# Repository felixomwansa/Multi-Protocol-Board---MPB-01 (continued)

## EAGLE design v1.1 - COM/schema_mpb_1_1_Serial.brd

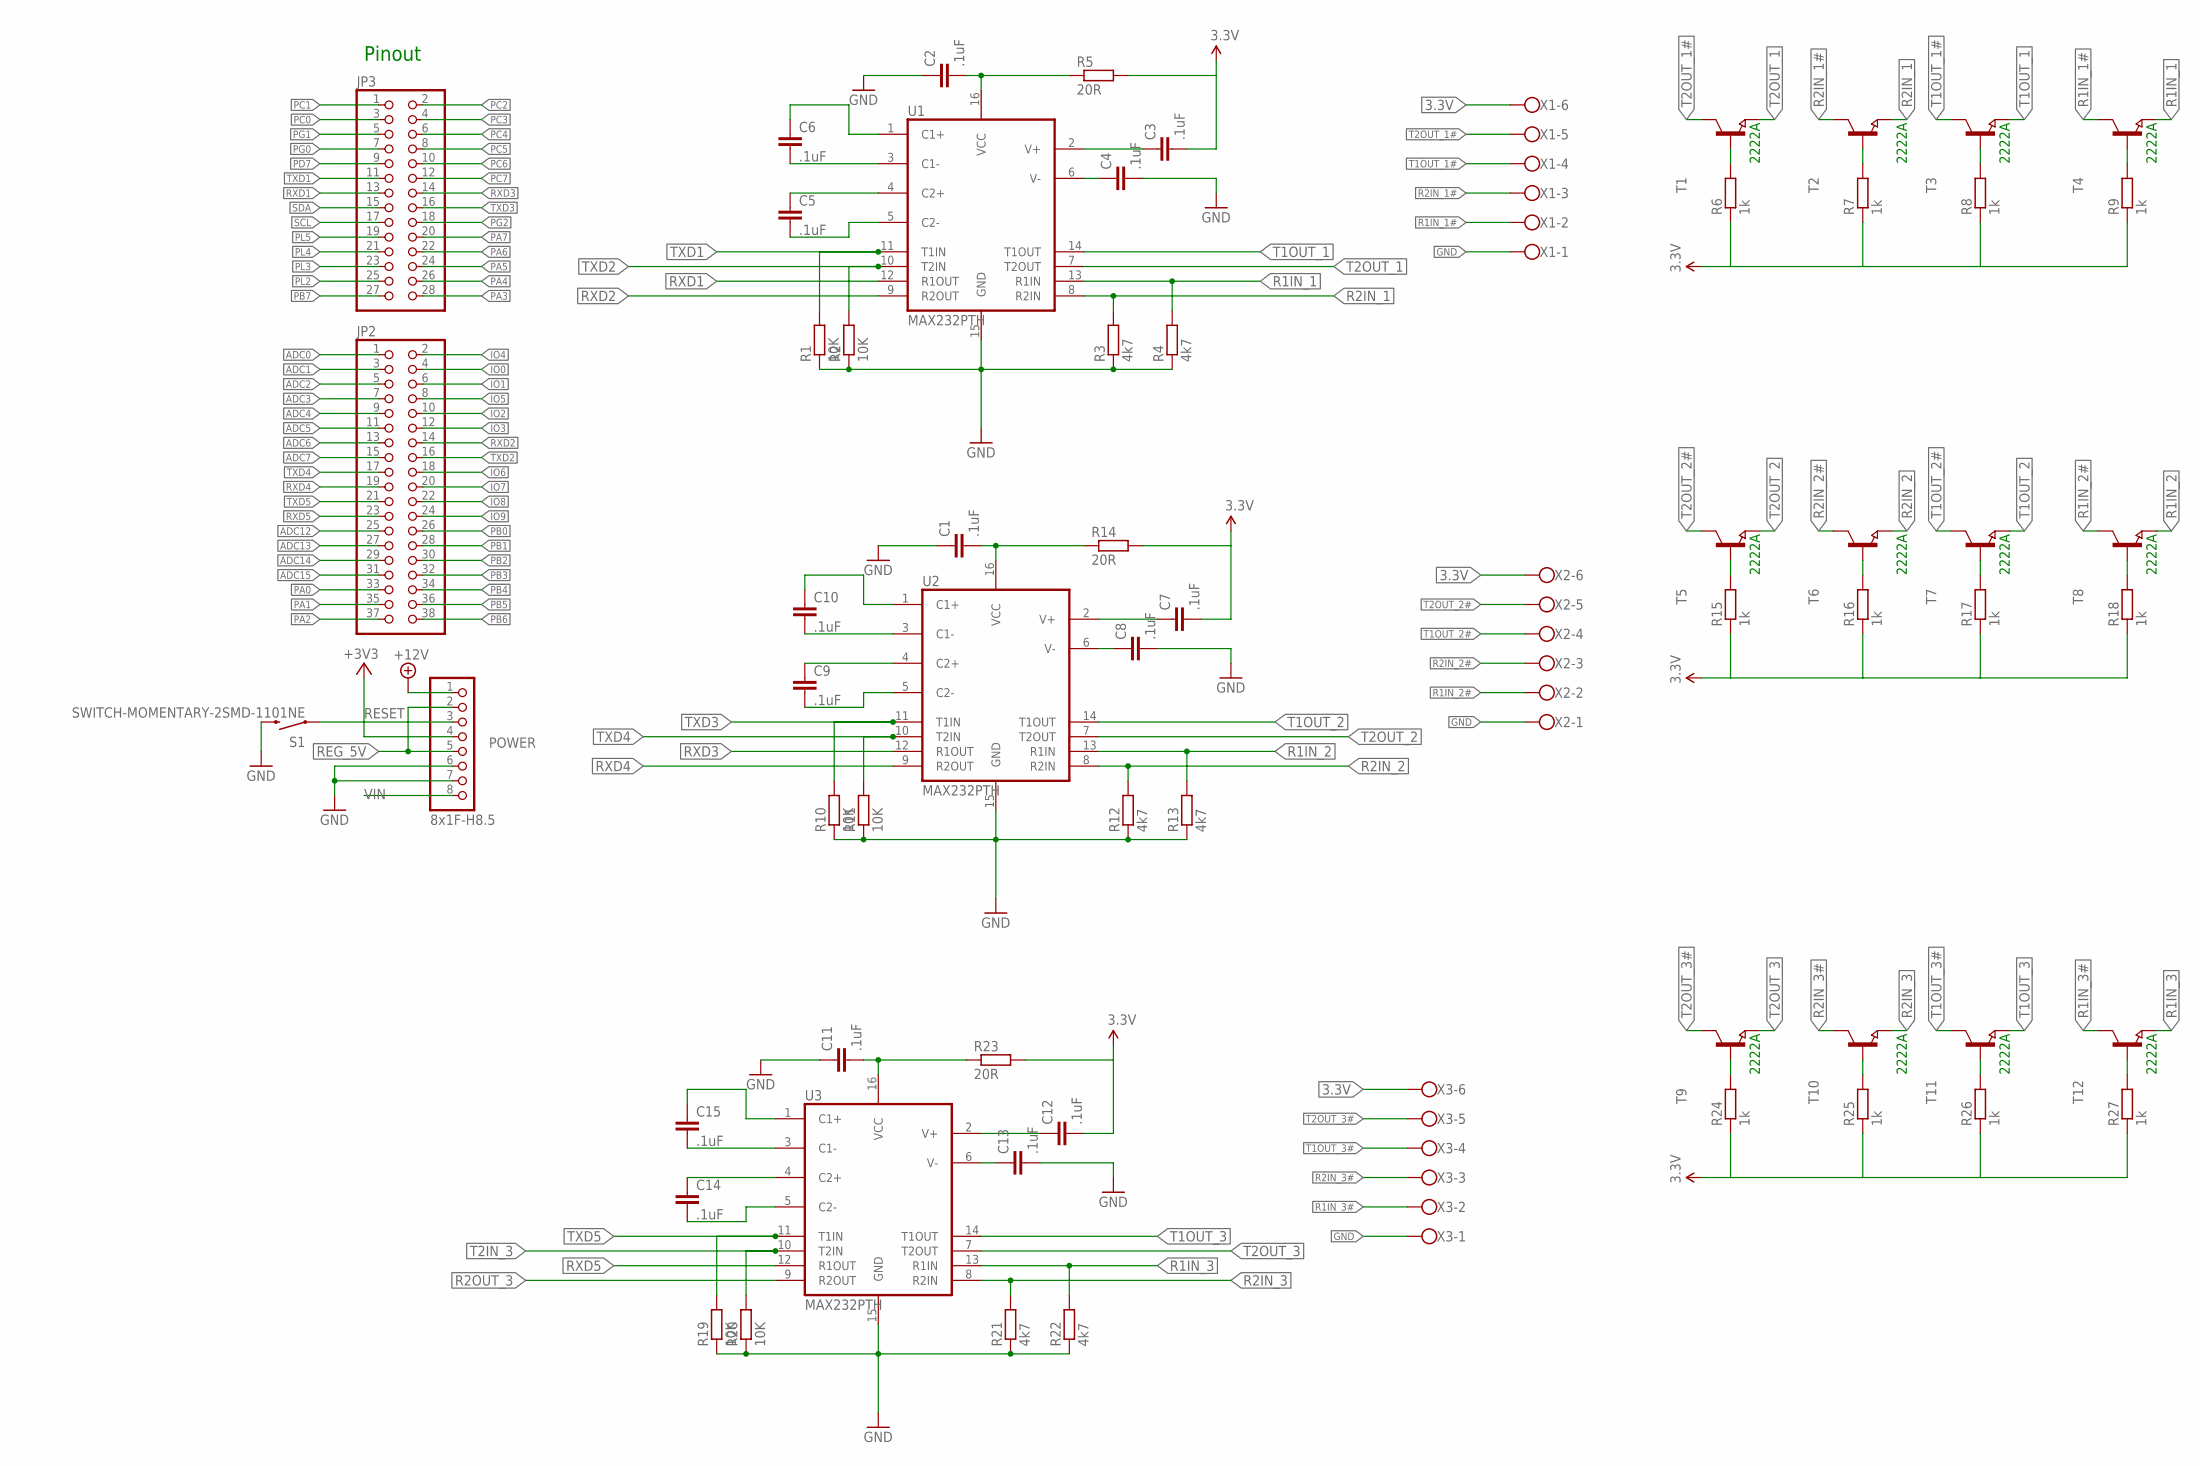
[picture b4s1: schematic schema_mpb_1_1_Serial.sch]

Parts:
C1, C2, C3, C4, C5, C6, C7, C8, C9, C10, C11, C12, C13, C14, C15: .1uF; C0805
JP2: PINHD-2X19; 2X19
JP3: PINHD-2X14; 2X14
POWER: 8x1F-H8.5; 1X08
R1, R2, R10, R11, R19, R20: 10K; R0805
R3, R4, R12, R13, R21, R22: 4k7; R0805
R5, R14, R23: 20R; R0805
R6, R7, R8, R9, R15, R16, R17, R18, R24, R25, R26, R27: 1k; R0805
S1: SWITCH-MOMENTARY-2SMD-1101NE; TACTILE-SWITCH-1101NE
T1, T2, T3, T4, T5, T6, T7, T8, T9, T10, T11, T12: NPN-TRANSISTOR_SOT23; SOT23
U1, U2, U3: MAX232PTH; DIL16
X1, X2, X3: W237-6

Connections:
3.3V: C3.2, C7.2, C12.2, POWER.4, R5.2, R6.1, R7.1, R8.1, R9.1, R14.2, R15.1, R16.1, R17.1, R18.1, R23.2, R24.1, R25.1, R26.1, R27.1, X1.6, X2.6, X3.6
+12V: POWER.1
ADC0: JP2.1
ADC1: JP2.3
ADC2: JP2.5
ADC3: JP2.7
ADC4: JP2.9
ADC5: JP2.11
ADC6: JP2.13
ADC7: JP2.15
ADC12: JP2.25
ADC13: JP2.27
ADC14: JP2.29
ADC15: JP2.31
GND: C1.1, C2.1, C4.2, C8.2, C11.1, C13.2, POWER.6, POWER.7, R1.1, R2.1, R3.1, R4.1, R10.1, R11.1, R12.1, R13.1, R19.1, R20.1, R21.1, R22.1, S1.2, U1.15 (GND), U2.15 (GND), U3.15 (GND), X1.1, X2.1, X3.1
IO0: JP2.4
IO1: JP2.6
IO2: JP2.10
IO3: JP2.12
IO4: JP2.2
IO5: JP2.8
IO6: JP2.18
IO7: JP2.20
IO8: JP2.22
IO9: JP2.24
unnamed: C10.2, U2.3 (C1-)
unnamed: C10.1, U2.1 (C1+)
unnamed: C9.2, U2.5 (C2-)
unnamed: C9.1, U2.4 (C2+)
unnamed: C8.1, U2.6 (V-)
unnamed: C1.2, R14.1, U2.16 (VCC)
unnamed: C7.1, U2.2 (V+)
unnamed: R15.2, T5.1 (B)
unnamed: R16.2, T6.1 (B)
unnamed: R17.2, T7.1 (B)
unnamed: R18.2, T8.1 (B)
unnamed: C15.2, U3.3 (C1-)
unnamed: C15.1, U3.1 (C1+)
unnamed: C14.2, U3.5 (C2-)
unnamed: C6.2, U1.3 (C1-)
unnamed: C6.1, U1.1 (C1+)
unnamed: C5.2, U1.5 (C2-)
unnamed: C5.1, U1.4 (C2+)
unnamed: C4.1, U1.6 (V-)
unnamed: C2.2, R5.1, U1.16 (VCC)
unnamed: C3.1, U1.2 (V+)
unnamed: R6.2, T1.1 (B)
unnamed: R7.2, T2.1 (B)
unnamed: R8.2, T3.1 (B)
unnamed: R9.2, T4.1 (B)
unnamed: C14.1, U3.4 (C2+)
unnamed: C13.1, U3.6 (V-)
unnamed: C11.2, R23.1, U3.16 (VCC)
unnamed: C12.1, U3.2 (V+)
unnamed: R24.2, T9.1 (B)
unnamed: R25.2, T10.1 (B)
unnamed: R26.2, T11.1 (B)
unnamed: R27.2, T12.1 (B)
PA0: JP2.33
PA1: JP2.35
PA2: JP2.37
PA3: JP3.28
PA4: JP3.26
PA5: JP3.24
PA6: JP3.22
PA7: JP3.20
PB0: JP2.26
PB1: JP2.28
PB2: JP2.30
PB3: JP2.32
PB4: JP2.34
PB5: JP2.36
PB6: JP2.38
PB7: JP3.27
PC0: JP3.3
PC1: JP3.1
PC2: JP3.2
PC3: JP3.4
PC4: JP3.6
PC5: JP3.8
PC6: JP3.10
PC7: JP3.12
PD7: JP3.9
PG0: JP3.7
PG1: JP3.5
PG2: JP3.18
PL2: JP3.25
PL3: JP3.23
PL4: JP3.21
PL5: JP3.19
R1IN_1: R4.2, T4.2 (E), U1.13 (R1IN)
R1IN_1#: T4.3 (C), X1.2
R1IN_2: R13.2, T8.2 (E), U2.13 (R1IN)
R1IN_2#: T8.3 (C), X2.2
R1IN_3: R22.2, T12.2 (E), U3.13 (R1IN)
R1IN_3#: T12.3 (C), X3.2
R2IN_1: R3.2, T2.2 (E), U1.8 (R2IN)
R2IN_1#: T2.3 (C), X1.3
R2IN_2: R12.2, T6.2 (E), U2.8 (R2IN)
R2IN_2#: T6.3 (C), X2.3
R2IN_3: R21.2, T10.2 (E), U3.8 (R2IN)
R2IN_3#: T10.3 (C), X3.3
R2OUT_3: U3.9 (R2OUT)
REG_5V: POWER.2, POWER.5
RESET: POWER.3, S1.1
RXD1: JP3.13, U1.12 (R1OUT)
RXD2: JP2.14, U1.9 (R2OUT)
RXD3: JP3.14, U2.12 (R1OUT)
RXD4: JP2.19, U2.9 (R2OUT)
RXD5: JP2.23, U3.12 (R1OUT)
SCL: JP3.17
SDA: JP3.15
T1OUT_1: T3.2 (E), U1.14 (T1OUT)
T1OUT_1#: T3.3 (C), X1.4
T1OUT_2: T7.2 (E), U2.14 (T1OUT)
T1OUT_2#: T7.3 (C), X2.4
T1OUT_3: T11.2 (E), U3.14 (T1OUT)
T1OUT_3#: T11.3 (C), X3.4
T2IN_3: R20.2, U3.10 (T2IN)
T2OUT_1: T1.2 (E), U1.7 (T2OUT)
T2OUT_1#: T1.3 (C), X1.5
T2OUT_2: T5.2 (E), U2.7 (T2OUT)
T2OUT_2#: T5.3 (C), X2.5
T2OUT_3: T9.2 (E), U3.7 (T2OUT)
T2OUT_3#: T9.3 (C), X3.5
TXD1: JP3.11, R1.2, U1.11 (T1IN)
TXD2: JP2.16, R2.2, U1.10 (T2IN)
TXD3: JP3.16, R10.2, U2.11 (T1IN)
TXD4: JP2.17, R11.2, U2.10 (T2IN)
TXD5: JP2.21, R19.2, U3.11 (T1IN)
VIN: POWER.8

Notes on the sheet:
Pinout
2222A

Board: 2 copper layers, 64 parts (0 on the bottom side), 72 nets, no tracks yet.

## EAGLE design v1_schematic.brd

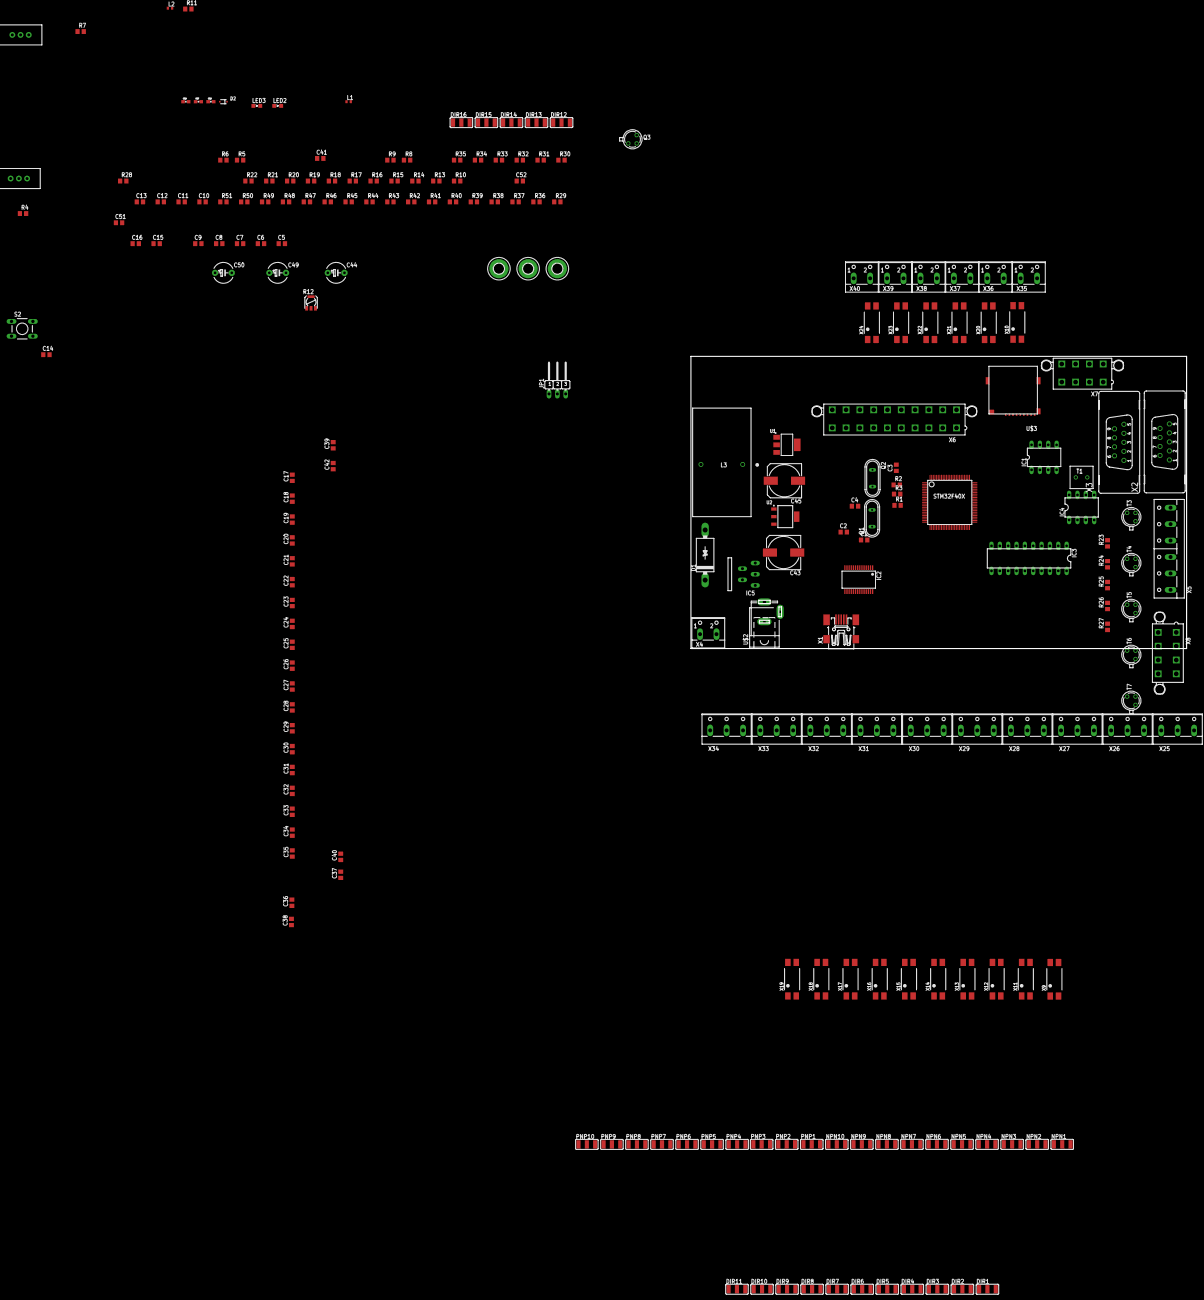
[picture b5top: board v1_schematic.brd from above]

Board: 2 copper layers, 150.8 x 88.9 mm, 212 parts (0 on the bottom side), 182 nets, no tracks yet.

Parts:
C1, C2: 20pF; C0805
C3, C4: 2pF; C0805
C5, C6, C7, C8, C9, C14, C15, C16, C17, C18, C19, C20, C21, C22, C23, C24, C25, C26, C27, C28, C29, C30, C31, C32, C33, C34, C35, C37, C38, C51: 100nF; C0805
C10, C11, C12, C13, C42, C52: 0.1uF; C0805
C36, C39: 4.7uF; C0805
C40, C41: 1uF; C0805
C43, C45: 47uF; 153CLV-1014
C44, C49: 1000uF 25V; E5-6
C46: 100nF; 0603-CAP
C47, C48: 47uF; 0603-CAP
C50: 100uF 25V; E5-6
D1: 1N5908; C4111-15
D2: BZX84J; SOD323(F)
DIR1, DIR2, DIR3, DIR4, DIR5, DIR6, DIR7, DIR8, DIR9, DIR10, DIR11, DIR12, DIR13, DIR14, DIR15, DIR16: SJ_2W
H1, H2, H3: MOUNT-PAD-ROUND3.2; 3,2-PAD
IC1: PCA82C250; DIL08
IC2: FT232RL; SSOP28
IC3: SP3223EBP; DIL20
IC4: MAX481CPA; DIL08
IC5: LM2576T; TO220-5
JP1: JP2W
L1, L2: BLM15HB121SN1; 0402
L3: PE-53116NL 220uH 50Hz; PE-53116NL
LED2, LED3: SML0805
NPN1, NPN2, NPN3, NPN4, NPN5, NPN6, NPN7, NPN8, NPN9, NPN10: SJ_2W
PNP1, PNP2, PNP3, PNP4, PNP5, PNP6, PNP7, PNP8, PNP9, PNP10: SJ_2W
Q1: 25MHz; QS
Q2: 32.768kHz; QS
Q3: 2N2222A; TO18
R1: 390; R0805
R2, R3, R11: 0; R0805
R4, R7, R8, R9, R10, R16, R18, R19, R28, R30, R31, R32, R33, R34, R35: 10K; R0805
R5, R6, R23, R24, R25, R26, R27: 1k; R0805
R12: 25K to 200K; PC25
R13, R14: 120; R0805
R15, R17: 20K; R0805
R20, R21, R22: 4k7; R0805
R29: 100R; R0805
R36, R37, R38, R39, R40, R41, R42, R43, R44, R45, R46, R47, R48, R49, R50, R51: 220R; R0805
S1, S3: STS121PC04
S2: DTS-6
T1: ST02-3.5MM; ED350V-02P
T3, T4, T5, T6, T7: 2N2222; TO18
U1: ON_SEMICONDUCTOR_NCP1117ST33T3GON_SEMICONDUCTOR_N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; ON_SEMICONDUCTOR_NCP1117ST33T3G_0
U2: ON_SEMICONDUCTOR_NCP1117ST50T3GON_SEMICONDUCTOR_N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; ON_SEMICONDUCTOR_NCP1117ST50T3G_2
U$1: STM32F40XSTM32D40X; LQFP100
U$2: SPC4078
U$3: MICROSD-PUSH-OUT
X1: MINI-USB-32005-201; 32005-201
X2, X3: F09VB
X4, X35, X36, X37, X38, X39, X40: W237-102
X5: W237-6
X6: 5566-20
X7, X8: 5566-8
X9, X10, X11, X12, X13, X14, X15, X16, X17, X18, X19, X20, X21, X22, X23, X24: PC817SW; PC817SMTW
X25, X26, X27, X28, X29, X30, X31, X32, X33, X34: W237-103

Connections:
+3V3: C17.1, C18.1, C19.1, C20.1, C21.1, C22.1, C23.1, C24.1, C25.1, C26.1, C27.1, C28.1, C29.1, C30.1, C31.1, C32.1, C33.1, C34.1, C35.1, C36.1, C39.1, C45.+, C46.1, C49.+, C52.1, L2.1, PNP1.1, PNP2.1, PNP3.1, PNP4.1, PNP5.1, PNP6.1, PNP7.1, PNP8.1, PNP9.1, PNP10.1, R23.2, R24.2, R25.2, R26.2, R27.2, S1.3, S3.3, U1.2, U1.4, U$1.11, U$1.19, U$1.28, U$1.50, U$1.75, U$1.100, U$3.4, X6.1, X6.2, X7.2, X8.2
+12V: C43.+, C44.+, C47.1, IC5.4, JP1.1, L3.2, U1.3, U2.3
BOOT0: R7.1, U$1.94
BOOT1: R4.2, U$1.37
CAN1_RX: IC1.1, U$1.70
CAN1_TX: IC1.4, U$1.71
CANH: IC1.7, R13.2, R14.2, X3.7
CANL: R13.1, R14.1, X3.2
COM1: X10.3, X35.2
COM2: X20.3, X36.2
COM3: X21.3, X37.2
COM4: X22.3, X38.2
COM5: X23.3, X39.2
COM6: X24.3, X40.2
DTR#: C51.2, IC2.2
ETH_MISO: U$1.31, U$1.53, X8.7
ETH_MOSI: U$1.32, U$1.54, X8.6
ETH_SCK: U$1.30, U$1.52, X8.4
ETH_SS: U$1.29, U$1.51, X8.3
GND: C1.2, C2.2, C3.2, C4.2, C5.2, C6.2, C7.2, C8.2, C9.2, C12.2, C13.2, C14.1, C15.2, C16.2, C17.2, C18.2, C19.2, C20.2, C21.2, C22.2, C23.2, C24.2, C25.2, C26.2, C27.2, C28.2, C29.2, C30.2, C31.2, C32.2, C33.2, C34.2, C35.2, C36.2, C37.2, C38.2, C39.2, C40.2, C41.2, C42.2, C43.-, C44.-, C45.-, C46.2, C47.2, C48.2, C49.-, C50.-, C52.2, D1.A, IC1.2, IC2.7, IC2.18, IC2.21, IC2.25, IC2.26, IC3.18, IC4.5, IC5.3, NPN1.3, NPN2.3, NPN3.3, NPN4.3, NPN5.3, NPN6.3, NPN7.3, NPN8.3, NPN9.3, NPN10.3, R8.2, R9.2, R10.2, R12.A, R15.1, R16.1, R18.1, R19.1, R20.1, R21.1, R28.1, R30.1, R31.1, R32.1, R33.1, R34.2, R35.2, S1.1, S2.1, S2.2, S3.1, T7.1, U2.1, U$1.10, U$1.20, U$1.27, U$1.74, U$1.99, U$2.3, U$3.6, U$3.G1, U$3.G2, U$3.G3, U$3.G4, X1.4, X1.5, X3.3, X4.1, X6.4, X6.6, X6.8, X6.10, X6.12, X6.14, X6.16, X6.18, X6.20, X7.1, X8.1, X8.5, X8.8, X9.3, X10.2, X11.3, X12.3, X13.3, X14.3, X15.3, X16.3, X17.3, X18.3, X19.3, X20.2, X21.2, X22.2, X23.2, X24.2, X25.1, X26.1, X27.1, X28.1, X29.1, X30.1, X31.1, X32.1, X33.1, X34.1
GND2: T7.3, X2.5, X5.6
IN1: DIR1.3, NPN1.1, PNP1.3, X25.2
IN2: DIR2.3, NPN2.1, PNP2.3, X26.2
IN3: DIR3.3, NPN3.1, PNP3.3, X27.2
IN4: DIR4.3, NPN4.1, PNP4.3, X28.2
IN5: DIR5.3, NPN5.1, PNP5.3, X29.2
IN6: DIR6.3, NPN6.1, PNP6.3, X30.2
IN7: DIR7.3, NPN7.1, PNP7.3, X31.2
IN8: DIR8.3, NPN8.1, PNP8.3, X32.2
IN9: DIR9.3, NPN9.1, PNP9.3, X33.2
IN10: DIR10.3, NPN10.1, PNP10.3, X34.2
unnamed: PNP1.2, R37.2
unnamed: C15.1, U$1.49
unnamed: C2.1, Q1.2, R1.1
unnamed: C5.1, L1.1, R22.2, X1.1
unnamed: C3.1, Q2.2, R3.1
unnamed: C4.1, Q2.1, R2.1
unnamed: C9.1, IC2.17
unnamed: R4.1, S1.2
unnamed: C7.1, IC2.16, X1.2
unnamed: C6.1, IC2.15, X1.3
unnamed: IC2.23, LED2.C
unnamed: IC2.22, LED3.C
unnamed: LED3.A, R6.2
unnamed: LED2.A, R5.2
unnamed: C10.2, IC3.4
unnamed: C11.2, IC3.6
unnamed: C11.1, IC3.5
unnamed: C10.1, IC3.2
unnamed: C13.1, IC3.7
unnamed: C12.1, IC3.3
unnamed: C14.2, S2.3, S2.4
unnamed: R7.2, S3.2
unnamed: IC4.7, T1.P$1
unnamed: IC1.8, R12.E
unnamed: IC4.6, T1.P$2
unnamed: D2.2, Q3.2, R16.2
unnamed: R37.1, X9.1
unnamed: Q3.1, R15.2
unnamed: NPN1.2, X9.2
unnamed: D2.1, R17.1
unnamed: JP1.2, X25.3, X26.3, X27.3, X28.3, X29.3, X30.3, X31.3, X32.3, X33.3, X34.3
unnamed: PNP8.2, R44.2
unnamed: C16.1, U$1.73
unnamed: D1.C, IC5.2, L3.1
unnamed: DIR1.2, X9.4
unnamed: R44.1, X17.1
unnamed: R23.1, T3.2
unnamed: R8.1, X6.11
unnamed: R24.1, T4.2
unnamed: R25.1, T5.2
unnamed: R9.1, X6.17
unnamed: R26.1, T6.2
unnamed: R27.1, T7.2
unnamed: R10.1, X6.19
unnamed: DIR11.2, R36.2
unnamed: R36.1, X10.1
unnamed: DIR12.2, R47.2
unnamed: PNP2.2, R38.2
unnamed: R38.1, X11.1
unnamed: NPN2.2, X11.2
unnamed: NPN8.2, X17.2
unnamed: DIR2.2, X11.4
unnamed: PNP3.2, R39.2
unnamed: R39.1, X12.1
unnamed: NPN3.2, X12.2
unnamed: DIR3.2, X12.4
unnamed: DIR8.2, X17.4
unnamed: PNP4.2, R40.2
unnamed: R40.1, X13.1
unnamed: NPN4.2, X13.2
unnamed: DIR4.2, X13.4
unnamed: PNP5.2, R41.2
unnamed: R41.1, X14.1
unnamed: NPN5.2, X14.2
unnamed: PNP9.2, R45.2
unnamed: DIR5.2, X14.4
unnamed: R45.1, X18.1
unnamed: PNP6.2, R42.2
unnamed: R42.1, X15.1
unnamed: NPN6.2, X15.2
unnamed: NPN9.2, X18.2
unnamed: DIR6.2, X15.4
unnamed: PNP7.2, R43.2
unnamed: R43.1, X16.1
unnamed: NPN7.2, X16.2
unnamed: DIR7.2, X16.4
unnamed: DIR9.2, X18.4
unnamed: PNP10.2, R46.2
unnamed: R46.1, X19.1
unnamed: NPN10.2, X19.2
unnamed: DIR10.2, X19.4
unnamed: R47.1, X20.1
unnamed: DIR13.2, R48.2
unnamed: R48.1, X21.1
unnamed: DIR14.2, R49.2
unnamed: R49.1, X22.1
unnamed: DIR15.2, R50.2
unnamed: R50.1, X23.1
unnamed: DIR16.2, R51.2
unnamed: R51.1, X24.1
NRF_CE: U$1.92, X7.3
NRF_CS: U$1.93, X7.4
NRF_IRQ: U$1.95, X7.8
NRF_MISO: U$1.90, X7.7
NRF_MOSI: U$1.91, X7.6
NRF_SCK: U$1.89, X6.13, X7.5
OUT1: DIR11.3, X10.4, X35.1
OUT2: DIR12.3, X20.4, X36.1
OUT3: DIR13.3, X21.4, X37.1
OUT4: DIR14.3, X22.4, X38.1
OUT5: DIR15.3, X23.4, X39.1
OUT6: DIR16.3, X24.4, X40.1
PC0: DIR1.1, U$1.15
PC1: DIR2.1, U$1.16
PC2: DIR3.1, U$1.17
PC3: DIR4.1, U$1.18
PC4: DIR5.1, U$1.33
PC5: DIR6.1, U$1.34
PC6: DIR7.1, U$1.63
PC13: DIR8.1, U$1.7
PC14: R3.2, U$1.8
PC15: R2.2, U$1.9
PD0: DIR9.1, U$1.81
PD1: DIR10.1, U$1.82
PD7: DIR11.1, U$1.88
PD8: DIR12.1, U$1.55
PD9: DIR13.1, U$1.56
PD10: DIR14.1, U$1.57
PD11: DIR15.1, U$1.58
PD12: DIR16.1, U$1.59
PH0: R1.2, U$1.12
PH1: C1.1, Q1.1, U$1.13
R1IN: IC3.16, R21.2, T6.1
R1IN_: T6.3, X2.2, X5.5
R2IN: IC3.9, R20.2, T4.1
R2IN_: T4.3, X5.4
RESET: C51.1, R29.1, U$1.14
RTS#: IC2.3, R29.2
SD_CMD: R31.2, U$1.83, U$3.3
SD_D0: R33.2, U$1.65, U$3.7
SD_D1: R34.1, U$1.66, U$3.8
SD_D2: R35.1, U$1.78, U$3.1
SD_D3: R32.2, U$1.79, U$3.2
SD_SCK: R30.2, U$1.80, U$3.5
T1OUT: IC3.17, T5.1
T1OUT_: T5.3, X2.3, X5.3
T2OUT: IC3.8, T3.1
TCK/SWCLK: U$1.76, X6.9
TDI: U$1.77, X6.5
TMS/SWDIO: U$1.72, X6.7
UART4_RX: IC3.15, R18.2, U$1.24
UART4_TX: IC3.13, R19.2, U$1.23
USART2_RTS: IC4.2, IC4.3, U$1.85
USART2_RX: IC4.1, U$1.26, U$1.87
USART2_TX: IC4.4, U$1.25, U$1.86
USART3_RX: IC2.1, U$1.48
USART3_TX: IC2.5, U$1.47
VCC: C8.1, C42.1, C48.1, IC1.3, IC2.4, IC2.19, IC2.20, IC3.19, IC3.20, IC4.8, L1.2, R5.1, R6.1, R22.1, R28.2, U2.2, U2.4, X5.1
VDDA: C37.1, C40.1, L2.2, R11.2, U$1.22
VIN: C50.+, IC5.1, Q3.3, R17.2, U$2.1, U$2.2, X4.2
VREF+: C38.1, C41.1, R11.1, U$1.21

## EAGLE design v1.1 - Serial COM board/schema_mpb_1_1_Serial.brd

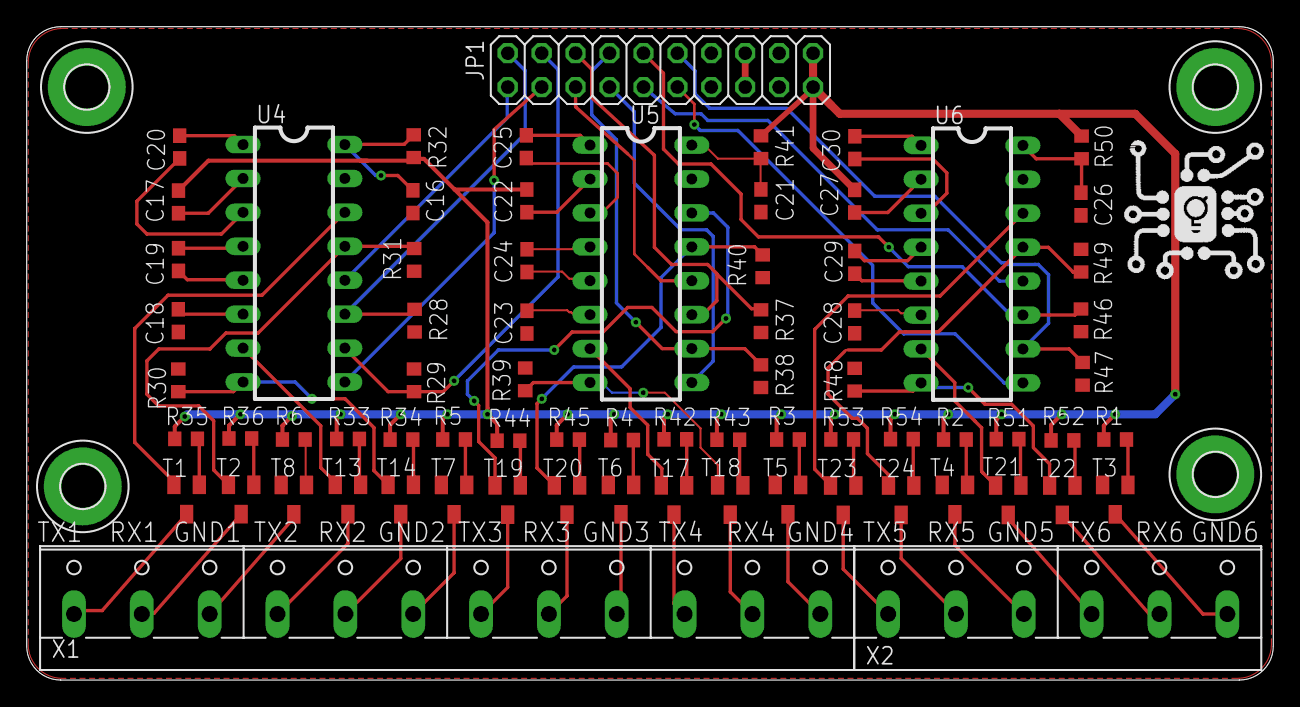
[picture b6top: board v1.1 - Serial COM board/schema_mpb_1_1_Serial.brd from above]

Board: 2 copper layers, 93.3 x 48.9 mm, 76 parts (0 on the bottom side), 84 nets.

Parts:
C16, C17, C18, C19, C20, C21, C22, C23, C24, C25, C26, C27, C28, C29, C30: .1uF; C0603
H1, H2, H3, H4: MOUNT-PAD-ROUND3.2; 3,2-PAD
JP1: 2X10
R1, R2, R3, R4, R5, R6, R33, R34, R35, R36, R42, R43, R44, R45, R51, R52, R53, R54: 1k; R0603
R28, R29, R37, R38, R46, R47: 10K; R0603
R30, R31, R39, R40, R48, R49: 4k7; R0603
R32, R41, R50: 20R; R0603
T1, T2, T3, T4, T5, T6, T7, T8, T13, T14, T17, T18, T19, T20, T21, T22, T23, T24: SOT23
U4, U5, U6: MAX232PTH; DIL16
X1: W237-12P
X2: W237-6P

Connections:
+3V3: C17.2, C22.2, C27.2, JP1.19, JP1.20, R1.1, R2.1, R3.1, R4.1, R5.1, R6.1, R32.2, R33.1, R34.1, R35.1, R36.1, R41.2, R42.1, R43.1, R44.1, R45.1, R50.2, R51.1, R52.1, R53.1, R54.1
+5V: JP1.15, JP1.16
GND: C16.1, C18.2, C21.1, C23.2, C26.1, C28.2, JP1.13, JP1.14, JP1.17, JP1.18, R28.1, R29.1, R30.1, R31.1, R37.1, R38.1, R39.1, R40.1, R46.1, R47.1, R48.1, R49.1, T3.2, T4.2, T5.2, T6.2, T7.2, T8.2, U4.15, U5.15, U6.15
GND1: T8.3, X1.3
GND2: T7.3, X1.6
GND3: T6.3, X1.9
GND4: T5.3, X1.12
GND5: T4.3, X2.3
GND6: T3.3, X2.6
unnamed: R1.2, T3.1
unnamed: R2.2, T4.1
unnamed: R3.2, T5.1
unnamed: R4.2, T6.1
unnamed: R5.2, T7.1
unnamed: R6.2, T8.1
unnamed: C20.2, U4.3
unnamed: C20.1, U4.1
unnamed: C19.2, U4.5
unnamed: C19.1, U4.4
unnamed: C18.1, U4.6
unnamed: C16.2, R32.1, U4.16
unnamed: C17.1, U4.2
unnamed: R33.2, T13.1
unnamed: R34.2, T14.1
unnamed: R35.2, T1.1
unnamed: R36.2, T2.1
unnamed: C25.2, U5.3
unnamed: C25.1, U5.1
unnamed: C24.2, U5.5
unnamed: C24.1, U5.4
unnamed: C23.1, U5.6
unnamed: C21.2, R41.1, U5.16
unnamed: C22.1, U5.2
unnamed: R42.2, T17.1
unnamed: R43.2, T18.1
unnamed: R44.2, T19.1
unnamed: R45.2, T20.1
unnamed: C30.2, U6.3
unnamed: C30.1, U6.1
unnamed: C29.2, U6.5
unnamed: C29.1, U6.4
unnamed: C28.1, U6.6
unnamed: C26.2, R50.1, U6.16
unnamed: C27.1, U6.2
unnamed: R51.2, T21.1
unnamed: R52.2, T22.1
unnamed: R53.2, T23.1
unnamed: R54.2, T24.1
RX1: JP1.1, U4.12
RX2: JP1.3, U4.9
RX3: JP1.5, U5.12
RX4: JP1.7, U5.9
RX5: JP1.9, U6.12
RX6: JP1.11, U6.9
RXD1: R31.2, T2.2, U4.13
RXD1#: T2.3, X1.2
RXD2: R30.2, T14.2, U4.8
RXD2#: T14.3, X1.5
RXD3: R40.2, T20.2, U5.13
RXD3#: T20.3, X1.8
RXD4: R39.2, T18.2, U5.8
RXD4#: T18.3, X1.11
RXD5: R49.2, T24.2, U6.13
RXD5#: T24.3, X2.2
RXD6: R48.2, T22.2, U6.8
RXD6#: T22.3, X2.5
TX1: JP1.2, R28.2, U4.11
TX2: JP1.4, R29.2, U4.10
TX3: JP1.6, R37.2, U5.11
TX4: JP1.8, R38.2, U5.10
TX5: JP1.10, R46.2, U6.11
TX6: JP1.12, R47.2, U6.10
TXD1: T1.2, U4.14
TXD1#: T1.3, X1.1
TXD2: T13.2, U4.7
TXD2#: T13.3, X1.4
TXD3: T19.2, U5.14
TXD3#: T19.3, X1.7
TXD4: T17.2, U5.7
TXD4#: T17.3, X1.10
TXD5: T23.2, U6.14
TXD5#: T23.3, X2.1
TXD6: T21.2, U6.7
TXD6#: T21.3, X2.4

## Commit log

2018-10-18 First Version Design of MPB
    Added barebones designs for MCU with FTDI UART Interface and SP3232 interface:
    - MCU: STM32F407xx, LQFP100 package
    - FTDI: FT232RL
    - SP3232: SP3223EBP
    - Added power connections to main MCUn and JTAG connector
2018-10-18 Decoupling and fixes
    - Added decoupling capacitor network to MCU
    - Fixes: conventions for component arrangement and enlargement of frame size
2018-10-19 Updates and fixes
    - completed RS232 interfacing, added DB9 connector
    - added CAN contoller interface with DB9 connector
2018-10-19 RS-485 Interface
    - added the rs-485 interface to MCU
2018-10-19 Organization
    - added sections to schematic
2018-10-19 Documentation
    - created folder for reference documents used
2018-10-24 Power Conversion and References
    - Completed power supply conversion for 5V (VCC) and 3V3.
    - Added STM32F407VETx pinout image for design reference.
2018-10-24 Corrections
    - Values for various passive parts adjusted.
2018-10-26 Ethernet Interface
    - added SPI ethernet module interface on SPI1, where MCU is SPI_master while W5100/W5500 module is SPI_slave
2018-12-03 RS232 Interface
    - Added protection circuitry
    - Corrected a few connections
2018-12-03 SD Card Interface
    - Added SD card interface based on
    SD MEMORY CARD PUSH-PUSH WITH CONNECTOR TYPE B
    Package Type: SDBMF-009XXBXX2
2018-12-04 Corrections
    - Adjusted FT2323 interface to USART1 and completed Interface connections
2018-12-04 Ethernet
    -Connected Ethernet interface to SPI2 - PB12-PB15
2018-12-04 SD Interface
    - Completed SD interfacing to SDIO of MCU (PD2, PC8-PC12)
2018-12-04 NRF Interface and corrections
    - Correction: Moved FT232 Interface to USART3
    - Completed NRF interface to SPI1 of MCU (PB3-PB8)
2018-12-04 Organization
    - Minor adjustments to arrangement
    - Added reference schematic for STMF4VEx
2018-12-06 GPIOs
    - Added input and output GPIO interfaces
2018-12-06 GPIOs
    - Added terminals for GPIO connection
2018-12-07 Updates
    - Completed GPIO-MCU connection
    - Changed labels to tags for easier visibility
2018-12-07 Mount-Pads
    Added mount Pads
2018-12-07 Created .brd file
2018-12-07 Board
    - Added dimension
2018-12-08 SD Card Interface
    - Changed interface to T-Flash Push-Out Micro SD Card Reader 14.75mm x 14.5mm SMD with external pins (smaller footprint)
2018-12-08 JTAG connector
    - Changed JTAG connector to dual row
2019-01-16 Minor Board Edits
2019-05-13 V2
    Created new layout template
2019-06-25 UPDATE
    Updated design for Main board and I/O
    - Reduced form factor, boards will be interconnected using ribbon cable connectors on 20-pin headers
2019-06-26 Routing
    First draft of routing tracks for main board
2019-06-28 Power Tracks
    Routed main power tracks for Main board PCB
2019-06-28 Board dimensions
    Added board dimensions
2019-06-28 First Draft
    Completed routing of first draft for main board
2019-06-28 Layer colours
    Changed layer colour fill to solid
2019-06-28 Orientation
    Changed board orientation to horizontal
2019-07-05 First Revision
    - Added 3 PIN terminal block for power
    - Cleaned up tracks /rerouted
2019-07-08 IO board tracks
    - Routed first version of IO board, added dimensions
2019-07-09 IO Board revision
    - Fixed GND airwires
    - Resolved width errors
2019-07-09 IO board. Routing from connector changed. GND vias added
2019-07-09 RS232 Board
    Routed tracks and added dimensions
2019-07-09 IO board
    - Added mounting holes and terminal labels
2019-07-10 Organisation
    - Created new folder for COM board
2019-07-11 Main board
    - Rounded corners (2.54mm setting)
    - Placed final mounting pad
2019-07-11 IO and Serial
    - Rounded corners
2019-07-11 Main board
    - Tidy routes
2019-07-12 Main board revisions
    - Rerouted long tracks to other layers
2019-07-16 Main board
    - Tidied tracks
2019-07-17 COM board
    - Routed first version of Wireless COM board
2019-07-17 Logos
    Added Geviton Logo to designs
2019-07-17 Main board
    Changed drill size of vias to 0.4mm
2019-07-17 Main board
    Applied ground stitching
2019-07-18 Wireless board
    - Changed drill sizes, got rid of via clearance issues
2019-08-02 IO board revision
    - Made Output traces thicker
    - Added pad for 5V/3.3V power for input sensors
2019-08-02 COM revision
    - Added Ethernet module outline
    - Adjusted track width
    - labelled CAN terminals
2019-08-02 Serial Board Revision
    - Labelled terminals
